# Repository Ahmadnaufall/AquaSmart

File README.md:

# 🌊 AquaSmart
## Deskripsi Proyek
AquaSmart adalah sistem otomatisasi berbasis Arduino Uno untuk pemberian pakan ikan dan monitoring kualitas air melalui pengukuran pH. Proyek ini bertujuan untuk mempermudah pemeliharaan akuarium atau kolam kecil dengan fitur kontrol pintar otomatis

# 🧠 ANGGOTA TEAM

|NAMA|NRP|JOBDESK|
|-----|----|------|
|Dhimas Fajar Kurniawan |2123600032| UI/UX Designer|
|Muhammad Nakhwa Zain | 2123600046 | Programmer |
|Ahmad Naufal Saifuddin | 2123600050 | Project Manager |
|Muhammad Jauhar Tsalis A. | 2123600051 | Hardware Specialist|
|Nur Cahyani | 2123600052 | Nonteknis |
|Ramatya Rimba Hamdhani | 2123600056 | 3D Designer |

## 🛠️ Fitur utama:

🚿 Monitoring pH air secara real-time

🐟 Pemberian pakan otomatis berbasis timer

📱 Peringatan otomatis ke pengguna saat pH air berada di luar batas normal

🔄 Kontrol manual pemberian pakan (menggunakan push button)

## 🛠️ Komponen Perangkat Keras
|Komponen | Fungsi |
|----------|---------|
|Arduino Uno | Otak dari sistem
|Sensor pH Air | Mengukur keasaman air
|Motor Servo | Mengontrol pemberian pakan
|LED & LCD | Indikator Perintah dijalankan |
|Breadboard & Jumper | Perakitan prototipe
|Power Supply | Menyediakan daya bagi sistem

## 📱 Tampilan Dashboard
Gauge untuk monitoring nilai pH

Notifikasi otomatis ketika pH tidak normaal

Indikasi untuk pemberian pakan manual (berjalannya perintah)

Timer untuk menunjukkan berapa waktu pemberian makan otomatis selanjutnya

## 📈 Alur Sistem
Arduino membaca data sensor pH secara berkala.

Data dikirim via UART ke Perangkat (web)

Blynk menampilkan nilai pH pada dashboard.

Jika pH >7 sistem mengirim notifikasi peringatan dan tampilan peringatan di LCD dan menyalanya Buzzer.

Timer internal memicu pemberian pakan secara otomatis.

Pengguna juga dapat memicu pemberian pakan manual melalui push button.

## 📊 MIND MAP BLOK DIAGRAM DAN FLOWCHART

### MIND MAP

### BLOK DIAGRAM

### FLOWCHART

### DESIGN FIGMA

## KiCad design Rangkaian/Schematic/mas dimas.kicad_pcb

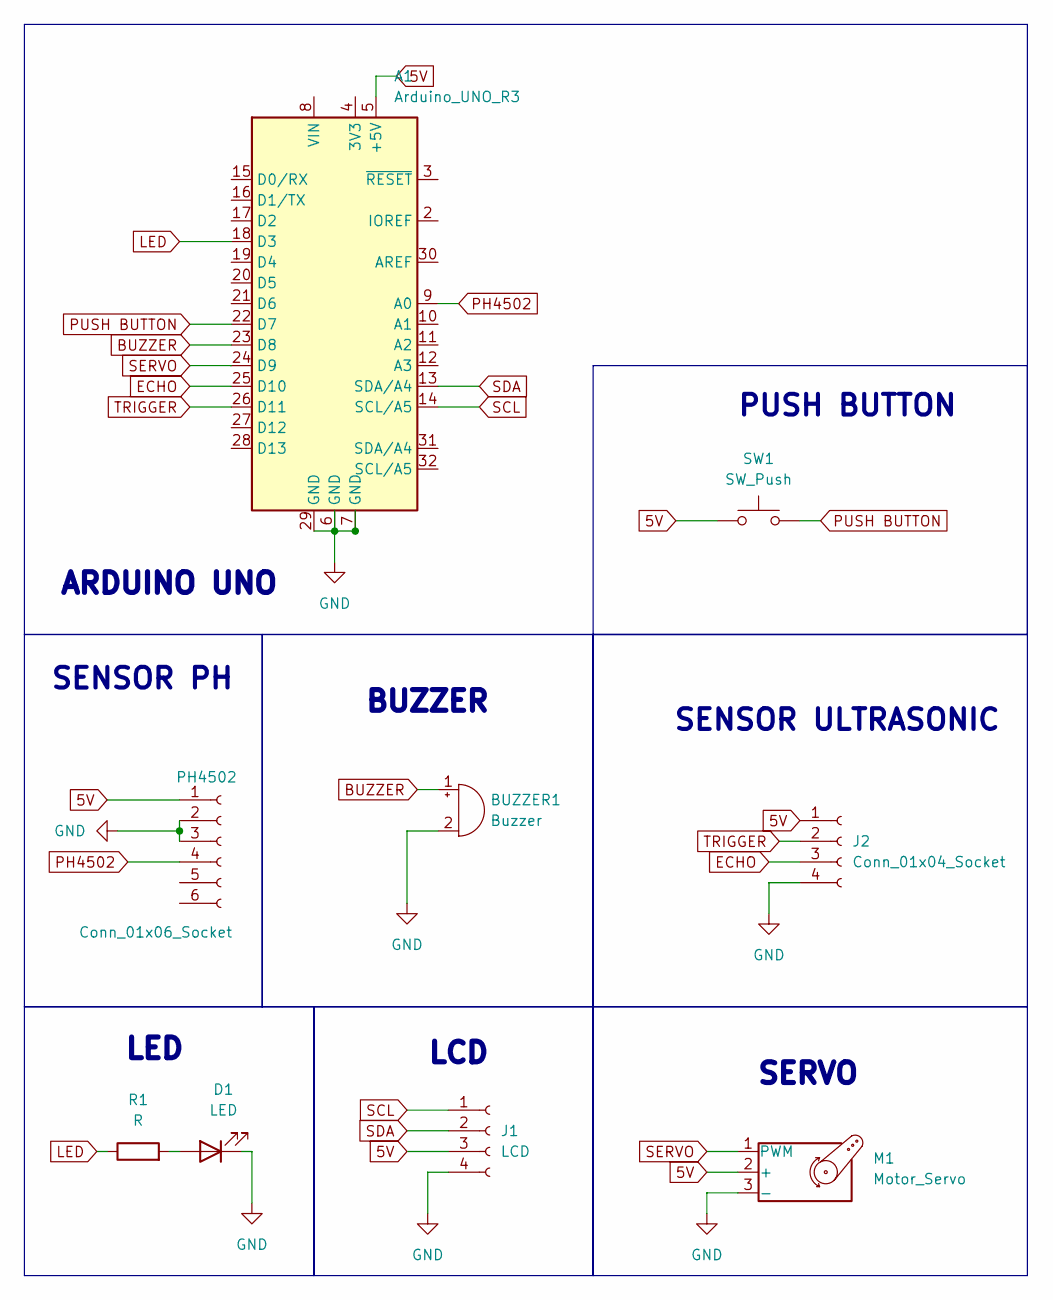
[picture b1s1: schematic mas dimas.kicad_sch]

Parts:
A1: Arduino_UNO_R3
BUZZER1: Buzzer; Buzzer_12x9.5RM7.6
D1: LED; LED_D1.8mm_W3.3mm_H2.4mm
J1: LCD; PinSocket_1x04_P2.54mm_Horizontal
J2: Conn_01x04_Socket; PinSocket_1x04_P2.54mm_Vertical
M1: Motor_Servo; PinHeader_1x03_P2.54mm_Vertical
PH4502: Conn_01x06_Socket; PinSocket_1x06_P2.54mm_Horizontal
R1: R; R_Axial_DIN0309_L9.0mm_D3.2mm_P15.24mm_Horizontal
SW1: SW_Push; PinSocket_1x03_P2.54mm_Vertical

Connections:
5V: A1.5 (+5V), J1.3, J2.1, M1.2 (+), PH4502.1, SW1.1
BUZZER: A1.23 (D8), BUZZER1.1 (+)
ECHO: A1.25 (D10), J2.3
GND: A1.6 (GND), A1.7 (GND), A1.29 (GND), BUZZER1.2 (-), D1.1 (K), J1.4, J2.4, M1.3 (-), PH4502.2, PH4502.3
LED: A1.18 (D3), R1.1
unnamed: D1.2 (A), R1.2
PH4502: A1.9 (A0), PH4502.4
PUSH BUTTON: A1.22 (D7), SW1.2
SCL: A1.14 (SCL/A5), J1.1
SDA: A1.13 (SDA/A4), J1.2
SERVO: A1.24 (D9), M1.1 (PWM)
TRIGGER: A1.26 (D11), J2.2

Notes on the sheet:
ARDUINO UNO
SERVO
SENSOR PH
BUZZER
SENSOR ULTRASONIC
LCD
LED
PUSH BUTTON

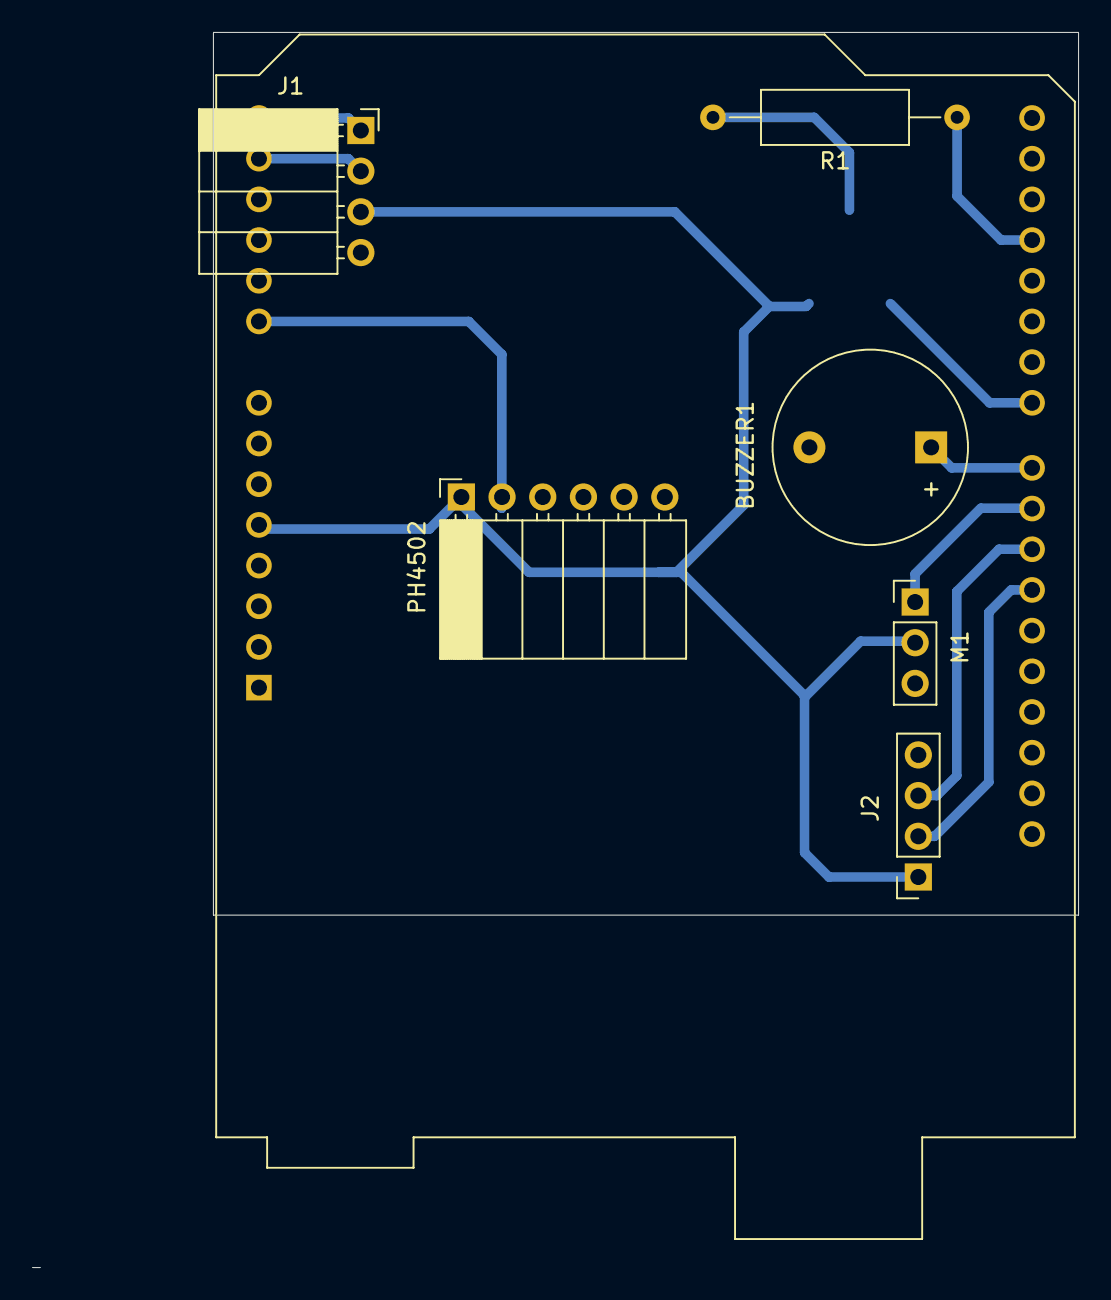
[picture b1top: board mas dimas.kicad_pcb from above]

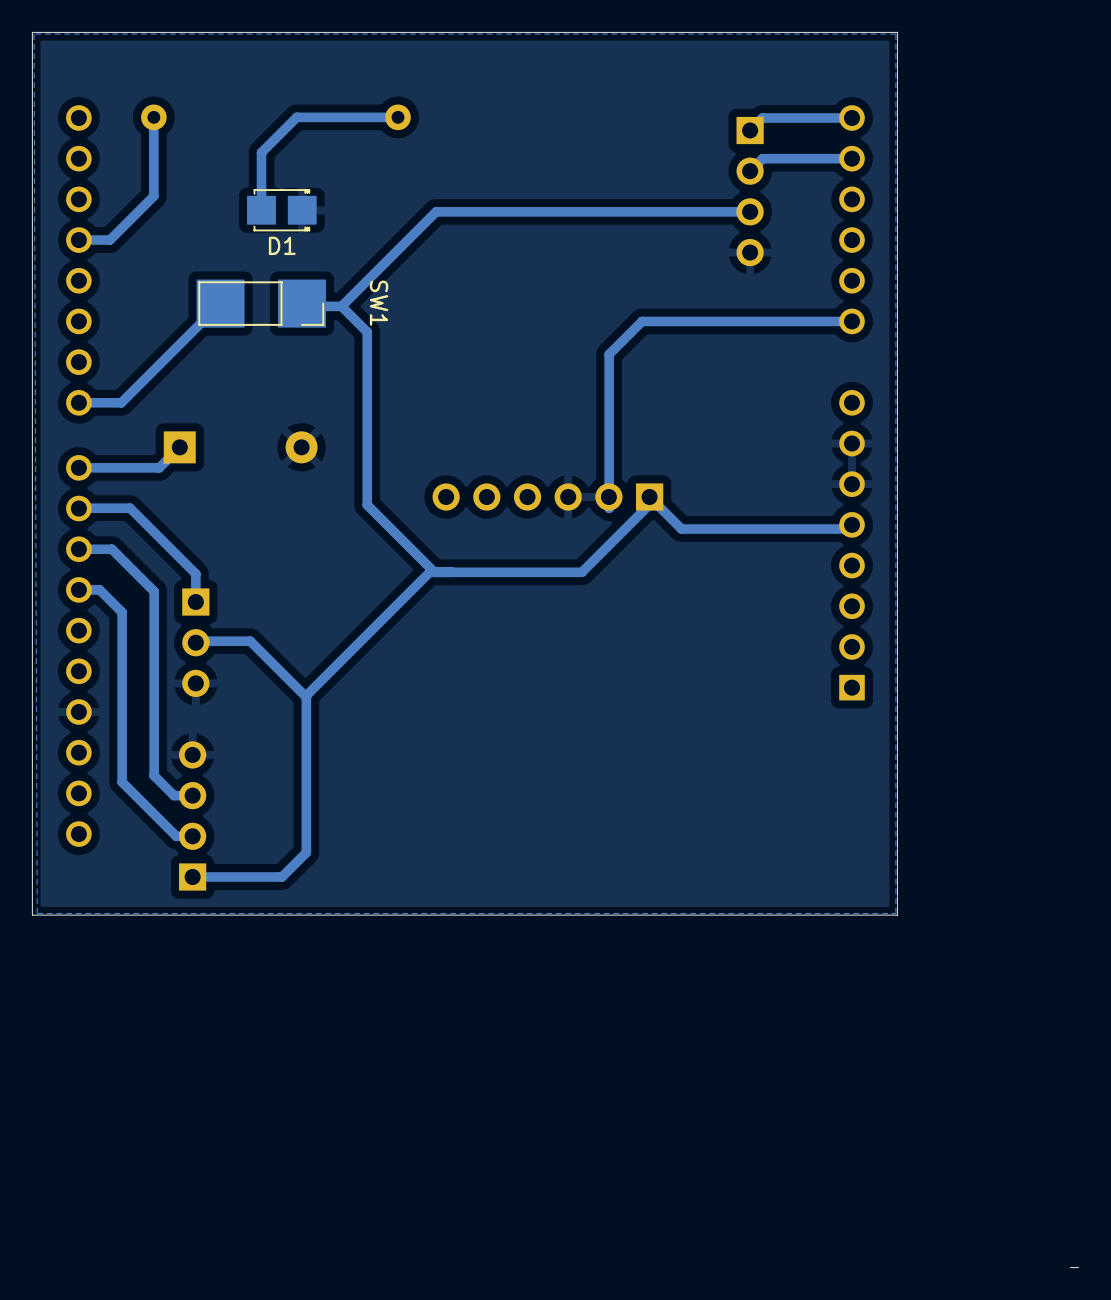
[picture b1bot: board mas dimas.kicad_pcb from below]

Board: 2 copper layers, 65.3 x 77.1 mm, 9 parts (2 on the bottom side), 12 nets.

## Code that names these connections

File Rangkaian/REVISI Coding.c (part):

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#define PH_SENSOR_CHANNEL 0
#define BUTTON_PIN PD7
#define LED_PIN PD3
#define SERVO_PIN PB1
#define BUZZER_PIN PB0
#define TRIG_PIN PB2
#define ECHO_PIN PB3

#define LCD_ADDR 0x27

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
// ---------- Servo ----------
void servo_init() {
    DDRB |= (1 << SERVO_PIN);
    TCCR1A = (1 << COM1A1) | (1 << WGM11);
    TCCR1B = (1 << WGM13) | (1 << WGM12) | (1 << CS11);
    ICR1 = 39999;
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
// ---------- Buzzer ----------
void buzzer_init() {
    DDRB |= (1 << BUZZER_PIN);
}

void buzzer_on(uint16_t frequency) {
    if (frequency == 0) return;
    uint16_t delay = (1000000UL / (2 * frequency));
    for (uint16_t i = 0; i < 100; i++) {
        PORTB |= (1 << BUZZER_PIN);
        _delay_us(delay);
        PORTB &= ~(1 << BUZZER_PIN);
        _delay_us(delay);
    }
}

void buzzer_off() {
    PORTB &= ~(1 << BUZZER_PIN);
}

// ---------- Utility ----------
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//-----------ultrasonik---------------
void ultrasonic_init() {
    DDRB |= (1 << TRIG_PIN);    // TRIG sebagai output
    DDRB &= ~(1 << ECHO_PIN);   // ECHO sebagai input
}

void trigger_ultrasonic() {
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

uint16_t read_echo_us() {
    while (!(PINB & (1 << ECHO_PIN))) {
        if (TCNT1 > 30000) return 0;
    }

    TCNT1 = 0;

    while (PINB & (1 << ECHO_PIN)) {
        if (TCNT1 > 30000) break;
    }

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
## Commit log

2025-04-21 Blok Diagram
2025-04-21 diagram blok.png
2025-04-21 Rename Blok Diagram to Blok Diagram.md
2025-04-21 Proposal dan PPT proyek Aqua Smart
2025-04-21 Create Rangkaian
2025-04-21 Gambar rangkaian
2025-04-21 Create 3D Model
2025-04-21 Create Test
2025-04-21 Create placeholder
2025-04-21 moving files
2025-04-22 Create Logo AquaSmart
2025-04-28 Rename LOGO AQUASMART.jpg to LOGOAQUASMART.jpg
2025-04-28 Rename diagram blok.png to Flowchart.png
2025-04-28 Create a
2025-05-01 Rename image.png to Gambar Rangkaian.png
2025-05-05 Create Coding
2025-05-05 Rename Coding to Coding.py
2025-05-08 diagram.json
2025-05-08 Coding.cpp
2025-05-18 design figma done
2025-05-19 Create Update GUI
2025-05-19 Create tampilan
2025-05-25 Rename Screenshot 2025-05-25 224118.png to REVISI Gambar Rangkaian
2025-05-25 Rename REVISI Gambar Rangkaian to REVISI Gambar Rangkaian.png
2025-05-25 Rename Coding.c to Coding_Simulasi.c
2025-05-25 Rename REVISI Coding.c to REVISI Coding_Simulasi.c
2025-05-30 Add files via upload
    File cover arduino stp
2025-06-03 Create Schematic
2025-06-03 Create aaa
